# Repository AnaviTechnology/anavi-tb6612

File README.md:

# ANAVI TB6612 Breakout Board

ANAVI TB6612 Breakout Board is a simple prototyping board for Toshiba TB6612FNG driver IC for dual DC motor.

# License

The project is released under the [Creative Commons Attribution-ShareAlike 4.0 International (CC BY-SA 4.0)](https://creativecommons.org/licenses/by-sa/4.0/).

Note: This is a human-readable summary of (and not a substitute for) the [license](https://creativecommons.org/licenses/by-sa/4.0/legalcode).

You are free to:

Share — copy and redistribute the material in any medium or format Adapt — remix, transform, and build upon the material for any purpose, even commercially. The licensor cannot revoke these freedoms as long as you follow the license terms. Under the following terms:

Attribution — You must give appropriate credit, provide a link to the license, and indicate if changes were made. You may do so in any reasonable manner, but not in any way that suggests the licensor endorses you or your use. ShareAlike — If you remix, transform, or build upon the material, you must distribute your contributions under the same license as the original. No additional restrictions — You may not apply legal terms or technological measures that legally restrict others from doing anything the license permits. Notices:

You do not have to comply with the license for elements of the material in the public domain or where your use is permitted by an applicable exception or limitation. No warranties are given. The license may not give you all of the permissions necessary for your intended use. For example, other rights such as publicity, privacy, or moral rights may limit how you use the material.

You will have to provide a link to the original creator of the project http://www.anavi.technology on any documentation or website.

Credit can be attributed through a link to the creator website: http://www.anavi.technology

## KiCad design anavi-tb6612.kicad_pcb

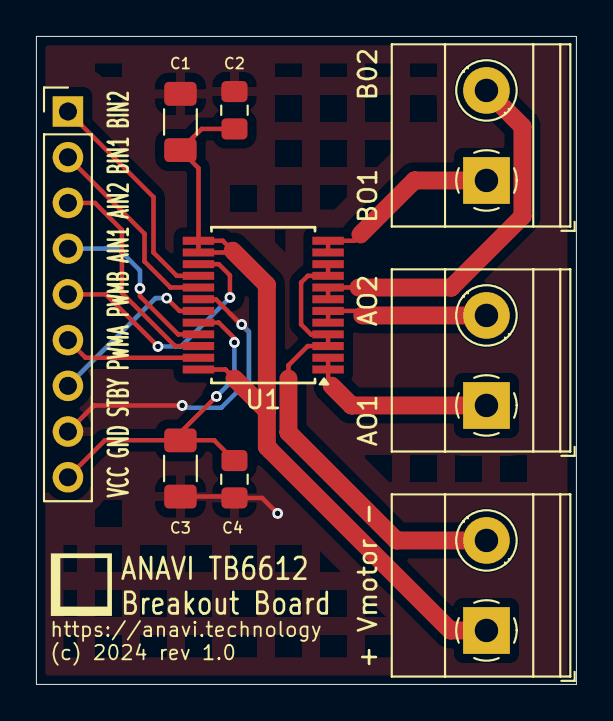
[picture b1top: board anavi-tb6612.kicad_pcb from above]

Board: 2 copper layers, 30.0 x 36.0 mm, 9 parts (0 on the bottom side), 15 nets.

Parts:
+ Vmotor -: Screw_Terminal_01x02; TerminalBlock_Phoenix_MKDS-1,5-2_1x02_P5.00mm_Horizontal
AO1     AO2: Screw_Terminal_01x02; TerminalBlock_Phoenix_MKDS-1,5-2_1x02_P5.00mm_Horizontal
BO1     B02: Screw_Terminal_01x02; TerminalBlock_Phoenix_MKDS-1,5-2_1x02_P5.00mm_Horizontal
C1, C3: 10uF; C_1206_3216Metric_Pad1.33x1.80mm_HandSolder
C2, C4: 0.1uF; C_0805_2012Metric_Pad1.18x1.45mm_HandSolder
J4: Conn_01x09; PinHeader_1x09_P2.54mm_Vertical
U1: TB6612FNG; SSOP-24_5.3x8.2mm_P0.65mm

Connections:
GND: C1.2, C2.2, C3.2, C4.2, J4.8, U1.18 (GND)
unnamed: AO1 AO2.1, U1.1 (AO1), U1.2 (AO1)
unnamed: AO1 AO2.2, U1.5 (AO2), U1.6 (AO2)
unnamed: BO1 B02.1, U1.11 (BO1), U1.12 (BO1)
unnamed: BO1 B02.2, U1.7 (BO2), U1.8 (BO2)
unnamed: + Vmotor -.1, C1.1, C2.1, U1.13 (VM2), U1.14 (VM3), U1.24 (VM1)
unnamed: + Vmotor -.2, U1.3 (PGND1), U1.4 (PGND1), U1.9 (PGND2), U1.10 (PGND2)
unnamed: J4.1, U1.16 (BIN2)
unnamed: J4.2, U1.17 (BIN1)
unnamed: J4.3, U1.22 (AIN2)
unnamed: J4.4, U1.21 (AIN1)
unnamed: J4.5, U1.15 (PWMB)
unnamed: J4.6, U1.23 (PWMA)
unnamed: J4.7, U1.19 (STBY)
unnamed: C3.1, C4.1, J4.9, U1.20 (VCC)

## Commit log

2024-08-30 Initialize project ANAVI TB6612
    Breakout board for Toshiba TB661FNG driver.

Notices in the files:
anavi-tb6612.kicad_pcb:
(c) 2024 rev 1.0
